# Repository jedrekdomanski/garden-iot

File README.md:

# 🌱 Garden IoT — Automated Irrigation System

An ESP32-based automated garden irrigation system that measures soil moisture, controls a water pump, and streams telemetry to AWS with real-time visualization via Grafana Cloud.

## Motivation

The idea behind this project was simple — being able to travel, go on holidays, or simply leave home for a day or two without worrying that the vegetables and herbs would die. Instead of relying on someone to water the plants or coming back to a dried-out garden, the system takes care of it automatically. It monitors soil moisture around the clock and waters only when needed, while giving full visibility into what's happening remotely through the Grafana dashboard.

The garden is also planned to grow over time — more plants, more zones, more automation. The system is designed with that in mind, making it easy to extend with additional sensors and devices as the garden expands.

## How it works

The ESP32 is a low-cost, low-power microcontroller with built-in WiFi and Bluetooth, widely used in IoT projects. It features a dual-core 240MHz processor, 520KB of RAM, and a deep sleep mode that draws only ~10µA — making it ideal for battery-powered or solar-powered applications. In this project it runs Arduino firmware compiled with PlatformIO and uses its built-in ADC to read the soil moisture sensor.

The ESP32 wakes from deep sleep every hour, measures soil moisture, decides whether to water, reports all events to AWS, then goes back to sleep. The entire active cycle takes only a few seconds, making it extremely power efficient.

### Measurement & watering logic

1. Powers the capacitive soil moisture sensor
2. Takes 10 averaged ADC readings for accuracy
3. Maps the raw value to a 0–100% moisture percentage using calibrated dry/wet values
4. If moisture is below the threshold (60%), triggers the MOSFET transistor to run the water pump for 20 seconds
5. Reports the outcome (`watering_started` / `watering_skipped`) to AWS
6. Goes back to deep sleep for 1 hour

### Events reported

| Event | Description |
|---|---|
| `device_boot` | Device woke up and connected to WiFi |
| `measurement_taken` | Soil moisture reading with raw value and percentage |
| `watering_started` | MOSFET triggered, irrigation started |
| `watering_finished` | MOSFET off, irrigation complete |
| `watering_skipped` | Soil moisture sufficient, watering not needed |
| `device_sleeping` | Device entering deep sleep |

## Hardware

| Component | Details |
|---|---|
| ESP32 DevKit | Dual-core 240MHz, built-in WiFi, deep sleep ~10µA |
| HW-080 Capacitive soil moisture sensor | GPIO 32 (ADC) |
| MOSFET transistor | GPIO 27 — switches power to the water pump |
| Water pump | 12V — controlled via MOSFET transistor |

## AWS Architecture

### Ingest pipeline
- **API Gateway** — HTTPS endpoint secured with a custom API key authorizer Lambda
- **Ingest Lambda** — validates and writes events to DynamoDB, forwards to EventBridge
- **DynamoDB** — stores all events with a 1-year TTL auto-expiry
- **EventBridge** — routes `measurement_taken` events with moisture < 30% to the alert Lambda
- **SES** — sends email alerts when soil moisture is critically low

### Visualization pipeline
- **Query Lambda** — queries DynamoDB and returns JSON, supports `from`, `to`, and `limit` parameters
- **Grafana Cloud** — polls `GET /metrics` via the Infinity datasource and renders the dashboard

## Grafana Dashboard

Three panels:
- **Current Moisture** — stat panel with color thresholds (green > 45%, yellow > 25%, red below)
- **Soil Moisture** — time series of moisture % over time
- **Event Log** — full table of all device events with timestamps

## Project structure

```
├── firmware/
│   └── garden/
│       ├── src/main.cpp        # ESP32 firmware
│       ├── include/secrets.h   # Generated secrets (git ignored)
│       ├── scripts/load_env.py # Injects .env into build
│       └── platformio.ini
└── terraform/
    ├── lambda/
    │   ├── ingest/handler.py   # Ingest Lambda
    │   ├── query/handler.py    # Query Lambda
    │   ├── authorizer/handler.py
    │   └── alert/handler.py
    ├── api_gateway.tf
    ├── dynamodb.tf
    ├── lambda.tf
    ├── eventbridge.tf
    ├── grafana.tf
    └── ses.tf
```

## Setup

### Prerequisites
- PlatformIO
- Terraform >= 1.6
- AWS CLI with a configured profile
- Grafana Cloud account (free tier)

### Firmware

1. Copy `firmware/.env.example` to `firmware/.env` and fill in your WiFi credentials and API endpoint
2. Build and flash with PlatformIO:
```bash
cd firmware/garden
pio run --target upload
```

### Infrastructure

1. Copy `terraform/terraform.tfvars.example` to `terraform/terraform.tfvars` and set your alert email
2. Deploy:
```bash
cd terraform
terraform init
terraform apply
```
3. Get your API endpoint and key:
```bash
terraform output api_endpoint
terraform output -raw api_key
```

### Grafana Cloud

1. Install the **Infinity** datasource plugin
2. Add a new Infinity datasource with header `x-api-key` set to your API key and allowed host set to your API Gateway domain
3. Create panels using `GET https://<api-endpoint>/metrics` as the data source URL

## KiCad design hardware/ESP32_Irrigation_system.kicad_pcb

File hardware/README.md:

# 🔌 Garden Irrigation System — PCB Hardware

A custom-designed PCB built around the ESP32 DevKit V1, created as part of my personal journey into electronics, IoT, and robotics. The board was designed in **KiCad 10** after several weeks of self-taught KiCad and electronics study.

## Overview

The board's primary purpose is to control a 12V water pump via a MOSFET transistor, as part of the automated garden irrigation system. It integrates power management monitoring, soil moisture sensing, pump control, and a safe programming switch into a single compact board.

## Features

### Soil Moisture Sensing
The board interfaces with a capacitive soil moisture sensor (HW-080) connected to the ESP32's ADC. The sensor provides real-time soil moisture readings that the microcontroller uses to decide whether to activate the water pump. If moisture drops below the configured threshold, the pump is triggered automatically.

### Pump Control via MOSFET
The water pump is switched on and off by a MOSFET transistor (1N4007 flyback diode included for protection against voltage spikes from the inductive pump load). The ESP32 drives the MOSFET gate directly from a GPIO pin.

### Power Supply
The ESP32 and board logic are powered by a custom-designed 3.3V solar-powered power management module:

👉 [Solar-Powered 3.3V Power Management PCB](https://github.com/jedrekdomanski/solar-charger-pcb)

The board includes battery voltage monitoring, allowing the firmware to track the power module's battery level.

### USB Programming Switch
A slide switch allows safe switching between two modes:

- **3.3V power on** — normal operation, powered by the power management module
- **3.3V power off + USB connected** — firmware upload mode

When flashing a firmware update, the workflow is:
1. Flip the slide switch to cut the 3.3V supply
2. Connect the USB cable to the ESP32
3. Upload the firmware via PlatformIO
4. Disconnect USB, flip the switch back to restore 3.3V power

This prevents conflicts between the USB power rail and the external 3.3V supply during programming.

## Components

| Component | Details |
|---|---|
| ESP32 DevKit V1 | Main microcontroller — WiFi, deep sleep, ADC |
| HW-080 capacitive soil moisture sensor | GPIO 32 (ADC) — triggers pump when moisture is too low |
| MOSFET transistor | Controls the 12V water pump via GPIO 27 |
| 1N4007 diode | Flyback protection for the pump |
| Slide switch | Isolates 3.3V supply during USB programming |
| Power management module | Custom 3.3V solar-powered PCB (see link above) |

## Design

Designed in **KiCad 10** — schematic and PCB layout files are located in this directory:

- `ESP32_Irrigation_system.kicad_sch` — schematic
- `ESP32_Irrigation_system.kicad_pcb` — PCB layout
- `ESP32_Irrigation_system.kicad_pro` — project file

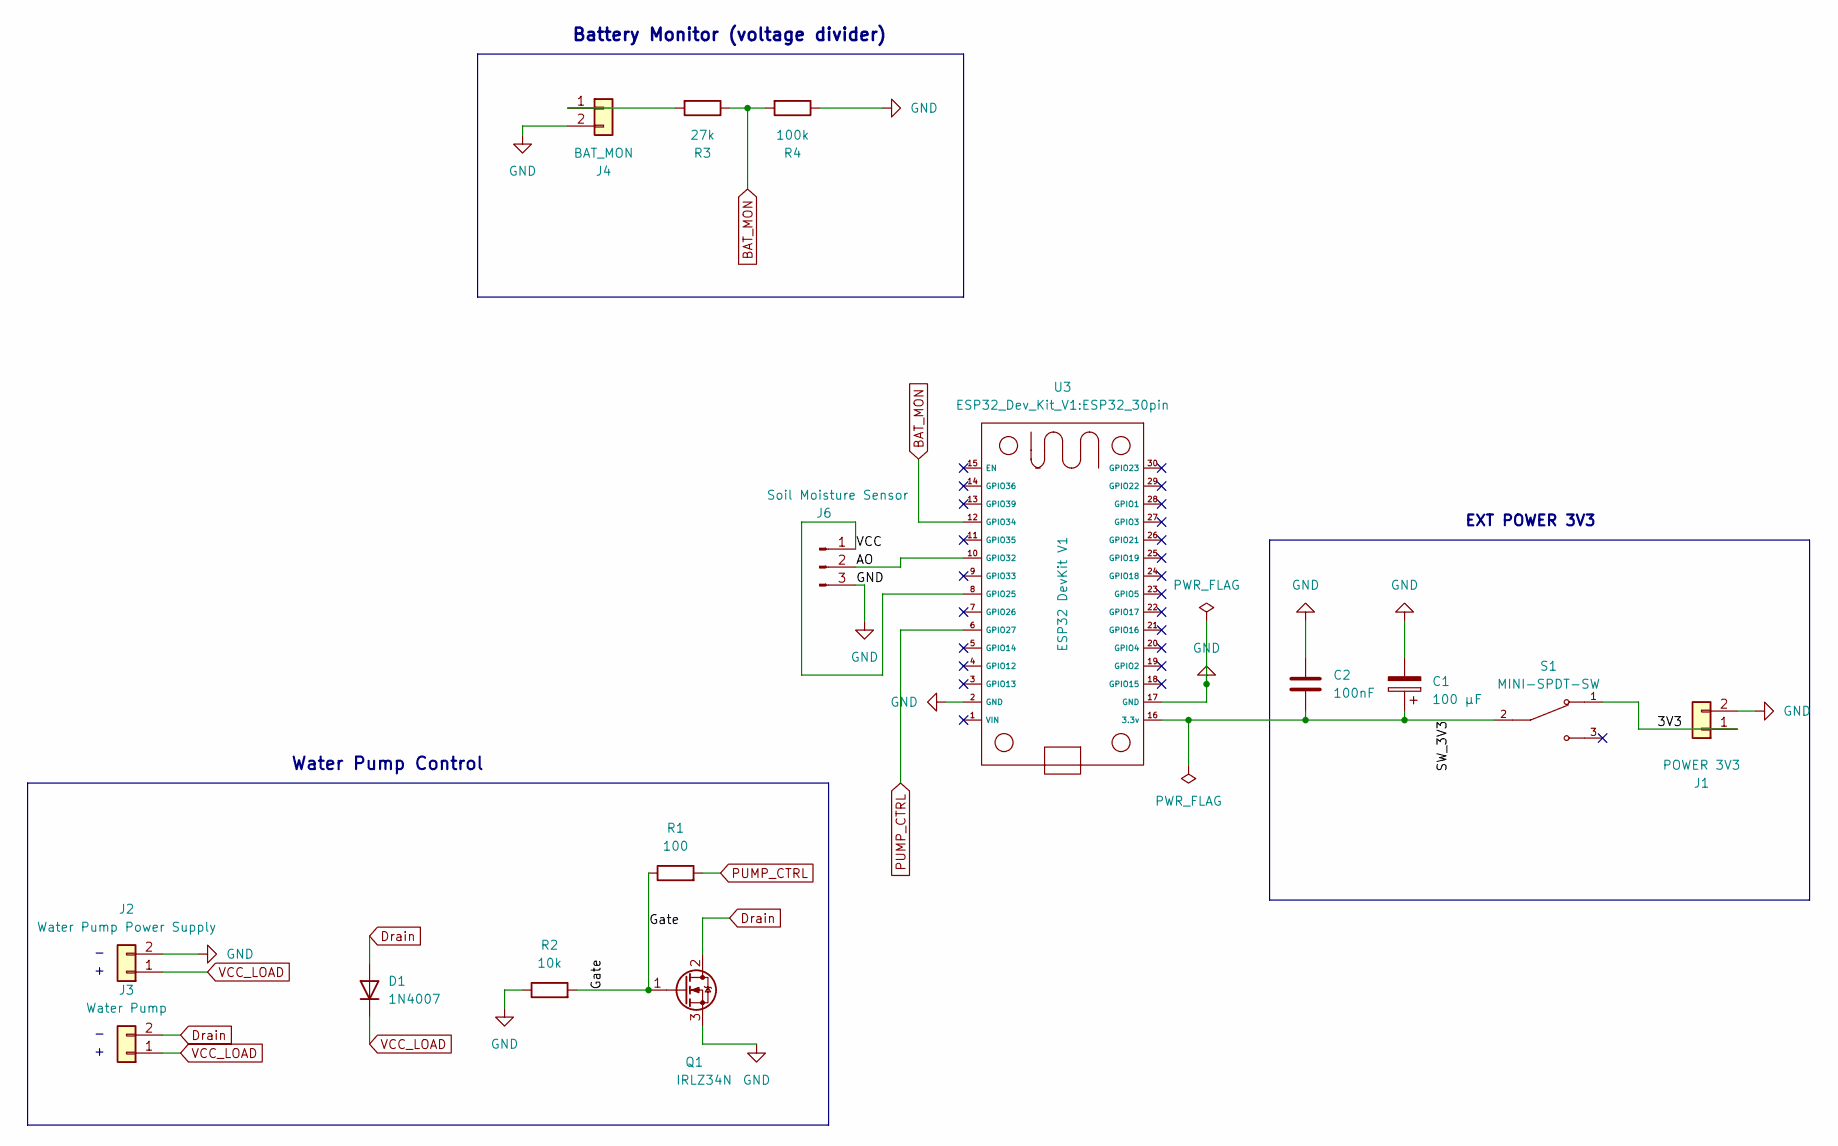
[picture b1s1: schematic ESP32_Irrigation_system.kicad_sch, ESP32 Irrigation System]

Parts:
C1: ‬‭‬‭‬‭‬‬‭‬‭‬‭‬‬‭‬‭‬‭‬100 μF; CP_Radial_D6.3mm_P2.50mm
C2: 100nF; C_Disc_D5.0mm_W2.5mm_P5.00mm
D1: 1N4007; D_DO-41_SOD81_P10.16mm_Horizontal
J1: POWER 3V3; TerminalBlock_Phoenix_MKDS-1,5-2-5.08_1x02_P5.08mm_Horizont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
J2: Water Pump Power Supply; TerminalBlock_Phoenix_MKDS-1,5-2-5.08_1x02_P5.08mm_Horizont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
J3: Water Pump; TerminalBlock_Phoenix_MKDS-1,5-2-5.08_1x02_P5.08mm_Horizont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
J4: BAT_MON; TerminalBlock_Phoenix_MKDS-1,5-2-5.08_1x02_P5.08mm_Horizont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
J6: Soil Moisture Sensor; PinHeader_1x03_P2.54mm_Vertical
Q1: IRLZ34N; TO-220-3_Vertical
R1: 100; R_Axial_DIN0207_L6.3mm_D2.5mm_P7.62mm_Horizontal
R2: 10k; R_Axial_DIN0207_L6.3mm_D2.5mm_P7.62mm_Horizontal
R3: 27k; R_Axial_DIN0207_L6.3mm_D2.5mm_P7.62mm_Horizontal
R4: 100k; R_Axial_DIN0207_L6.3mm_D2.5mm_P7.62mm_Horizontal
S1: MINI-SPDT-SW; SW_MINI-SPDT-SW; PARTREV C
U3: ESP32 DevKit V1; ESP32_30pin

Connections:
/3V3: J1.1, S1.1
/AO: J6.2, U3.10 (GPIO32)
/Gate: Q1.1 (G), R1.1, R2.2
/SW_3V3: C1.1, C2.2, S1.2, U3.16 (3.3v)
/VCC: J6.1, U3.8 (GPIO25)
BAT_MON: R3.1, R4.2, U3.12 (GPIO34)
Drain: D1.2 (A), J3.2, Q1.2 (D)
GND: C1.2, C2.1, J1.2, J2.2, J4.2, J6.3, Q1.3 (S), R2.1, R4.1, U3.2 (GND), U3.17 (GND)
unnamed: J4.1, R3.2
PUMP_CTRL: R1.2, U3.6 (GPIO27)
VCC_LOAD: D1.1 (K), J2.1, J3.1

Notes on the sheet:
EXT POWER 3V3
Water Pump Control
Battery Monitor (voltage divider)

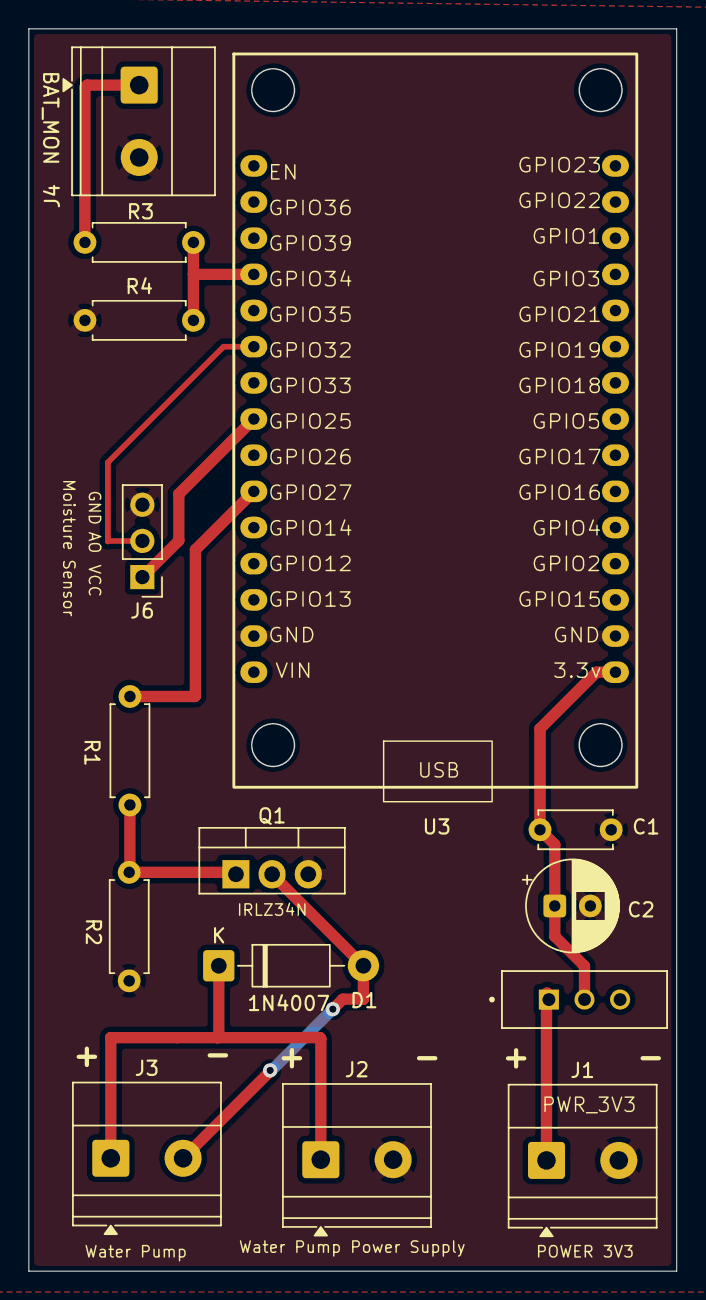
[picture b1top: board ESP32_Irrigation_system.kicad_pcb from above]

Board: 2 copper layers, 45.5 x 87.3 mm, 15 parts (0 on the bottom side), 11 nets.

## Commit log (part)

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2026-06-07 Add ready project
2026-06-07 Add README
2026-06-07 Add README (#1)
2026-06-07 Remove AWS rules
2026-06-07 Remove AWS rules (#2)
2026-06-07 Remove .amazonq rules from tracking
2026-06-07 Remove .amazonq rules from tracking (#3)
2026-06-07 Update readme (#4)
2026-06-10 Add hardware diagram
2026-06-10 Reorder sections
2026-06-10 Add models to hardware
2026-06-10 Add hardware diagram (#5)
    * Add hardware diagram
    * Reorder sections
    * Add models to hardware
2026-06-10 Update watering threashold
2026-06-10 Water for 7 seconds
2026-06-10 Update firmware to water for 7 seconds and change threashold to 50% (#6)
    * Update watering threashold
    * Water for 7 seconds
2026-06-11 Lengthen watering to 30 seconds
2026-06-11 Lengthen watering to 30 seconds (#7)
